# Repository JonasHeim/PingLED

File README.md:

Work in progress

# PingLED

Display the latency/delay to an internet node (e.g. Google) on a 7-segment display using a ESP8266 interfacing a TM1637.

Using the [ESP8266_NON_OS_SDK](https://github.com/espressif/ESP8266_NONOS_SDK)

## Compile application using make:
```
cd ./PingLED
make 
```
Change the variables
- COMPILE
- BOOT
- APP
- SPI_SPEED
- SPI_MODE

in ./PingLED/Makefile according to your configuration.
For additional information about the configuration see the [Expressif documentation](https://github.com/espressif/ESP8266_NONOS_SDK/tree/master/examples).

## Clean application:
```
cd ./PingLED
make clean
```

  ## Project structure:
  * ESP8266
    - Source code for the firmware on ESP8266
  * Documentation
    - Datasheets for TM1637
    - ESP8266 SDK documentation

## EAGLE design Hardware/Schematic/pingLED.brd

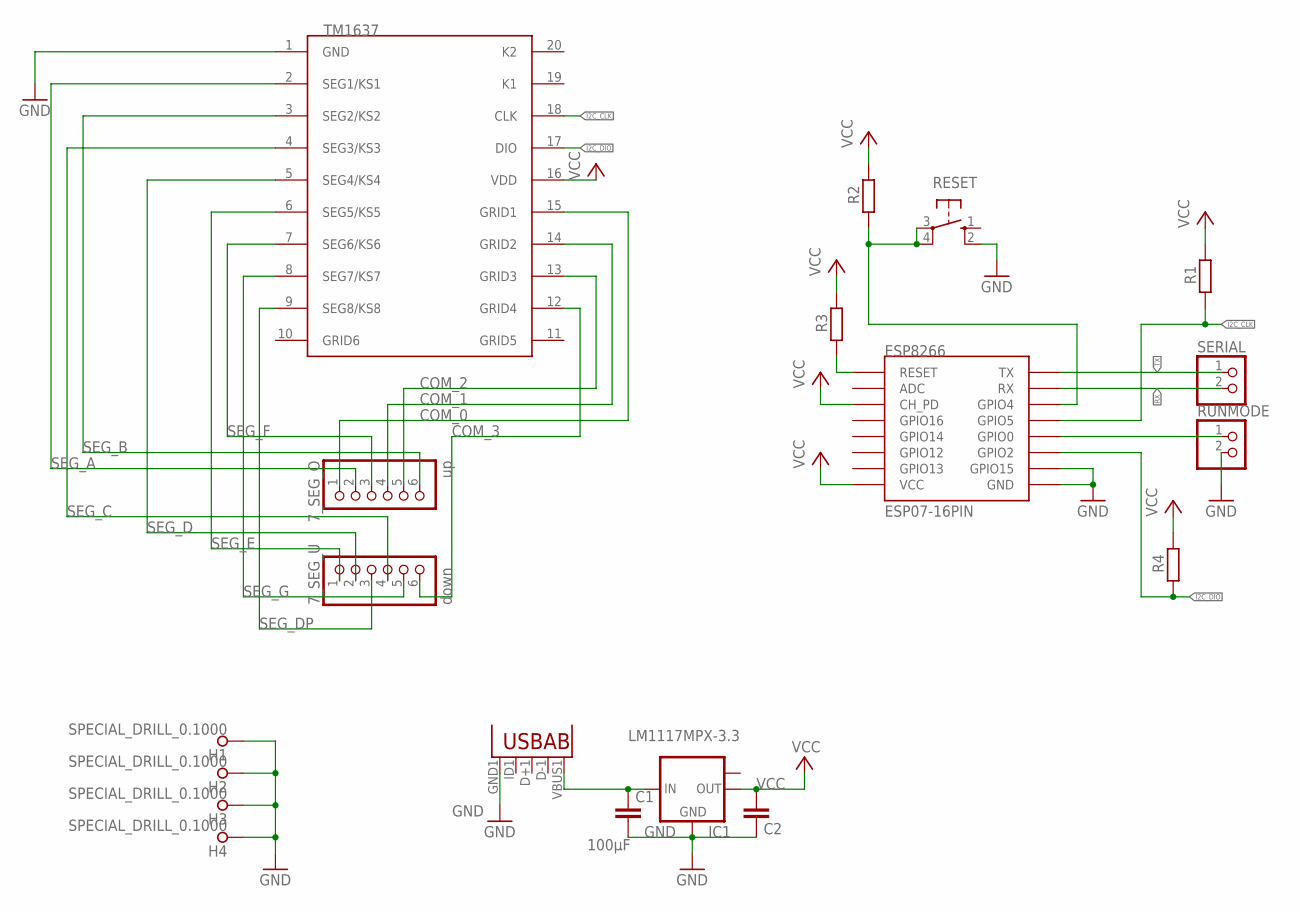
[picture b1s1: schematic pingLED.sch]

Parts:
7SEG_DRIVER: TM1637SOP20; SOIC127P1045X255-20
7_SEG_O: up; 1X06
7_SEG_U: down; 1X06
C1: 100µF; C0603
C2: C-EUC0603; C0603
ESP8266: ESP07-16PIN
H1, H2, H3, H4: SPECIAL_DRILL_0.1000; PAD_0.1000
IC1: LM1117MPX-3.3; SOT223
R1, R2, R3, R4: R-EU_R0603; R0603
RESET: 10-XX; B3F-10XX
RUNMODE: PINHD-1X2; 1X02
SERIAL: PINHD-1X2; 1X02
U1: V_IN; USB-MICRO-SMD

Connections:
COM_0: 7SEG_DRIVER.15 (GRID1), 7_SEG_O.1
COM_1: 7SEG_DRIVER.14 (GRID2), 7_SEG_O.4
COM_2: 7SEG_DRIVER.13 (GRID3), 7_SEG_O.5
COM_3: 7SEG_DRIVER.12 (GRID4), 7_SEG_U.6
GND: 7SEG_DRIVER.1 (GND), C1.2, C2.2, ESP8266.GND, ESP8266.GPIO15, H1.1, H2.1, H3.1, H4.1, IC1.1 (GND), RESET.2 (S1), RUNMODE.2, U1.GND1 (GND)
I2C_CLK: 7SEG_DRIVER.18 (CLK), ESP8266.GPIO5, R1.1
I2C_DIO: 7SEG_DRIVER.17 (DIO), ESP8266.GPIO2, R4.1
unnamed: ESP8266.GPIO0, RUNMODE.1
unnamed: ESP8266.GPIO4, R2.1, RESET.3, RESET.4 (P1)
unnamed: ESP8266.REST (RESET), R3.1
unnamed: C1.1, IC1.3 (IN), U1.VBUS1 (VBUS)
RX: ESP8266.RX, SERIAL.2
SEG_A: 7SEG_DRIVER.2 (SEG1/KS1), 7_SEG_O.2
SEG_B: 7SEG_DRIVER.3 (SEG2/KS2), 7_SEG_O.6
SEG_C: 7SEG_DRIVER.4 (SEG3/KS3), 7_SEG_U.4
SEG_D: 7SEG_DRIVER.5 (SEG4/KS4), 7_SEG_U.2
SEG_DP: 7SEG_DRIVER.9 (SEG8/KS8), 7_SEG_U.3
SEG_E: 7SEG_DRIVER.6 (SEG5/KS5), 7_SEG_U.1
SEG_F: 7SEG_DRIVER.7 (SEG6/KS6), 7_SEG_O.3
SEG_G: 7SEG_DRIVER.8 (SEG7/KS7), 7_SEG_U.5
TX: ESP8266.TX, SERIAL.1
VCC: 7SEG_DRIVER.16 (VDD), C2.1, ESP8266.CH_PD, ESP8266.VCC, IC1.2 (OUT), R1.2, R2.2, R3.2, R4.2

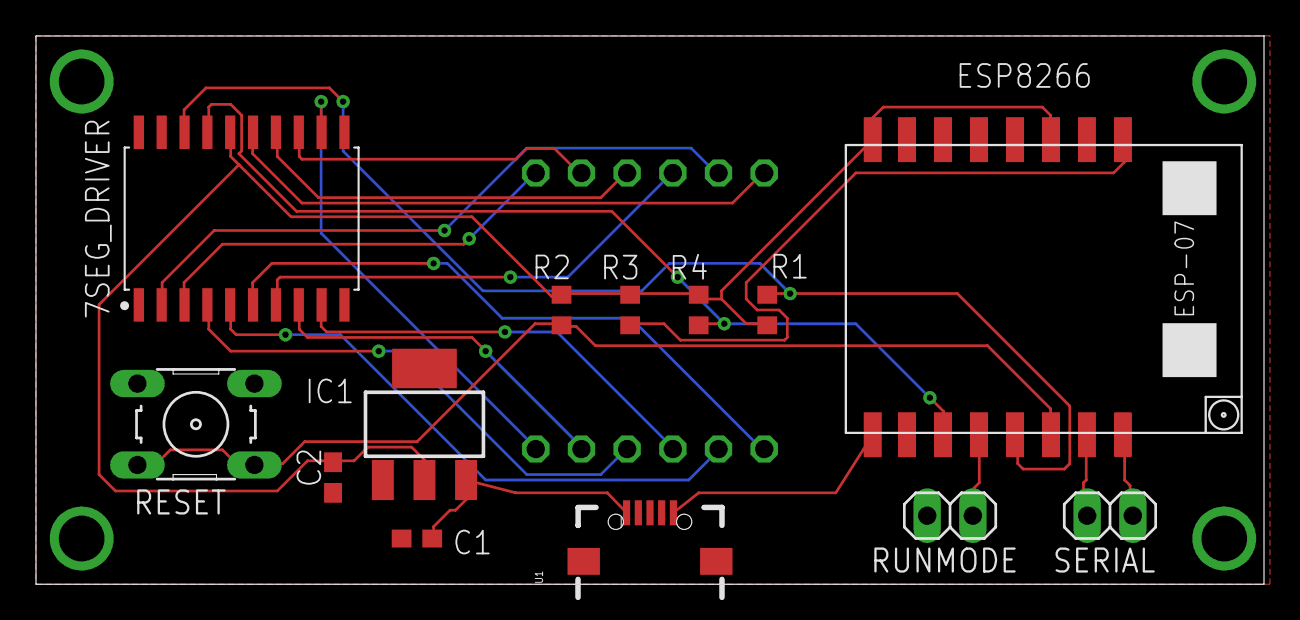
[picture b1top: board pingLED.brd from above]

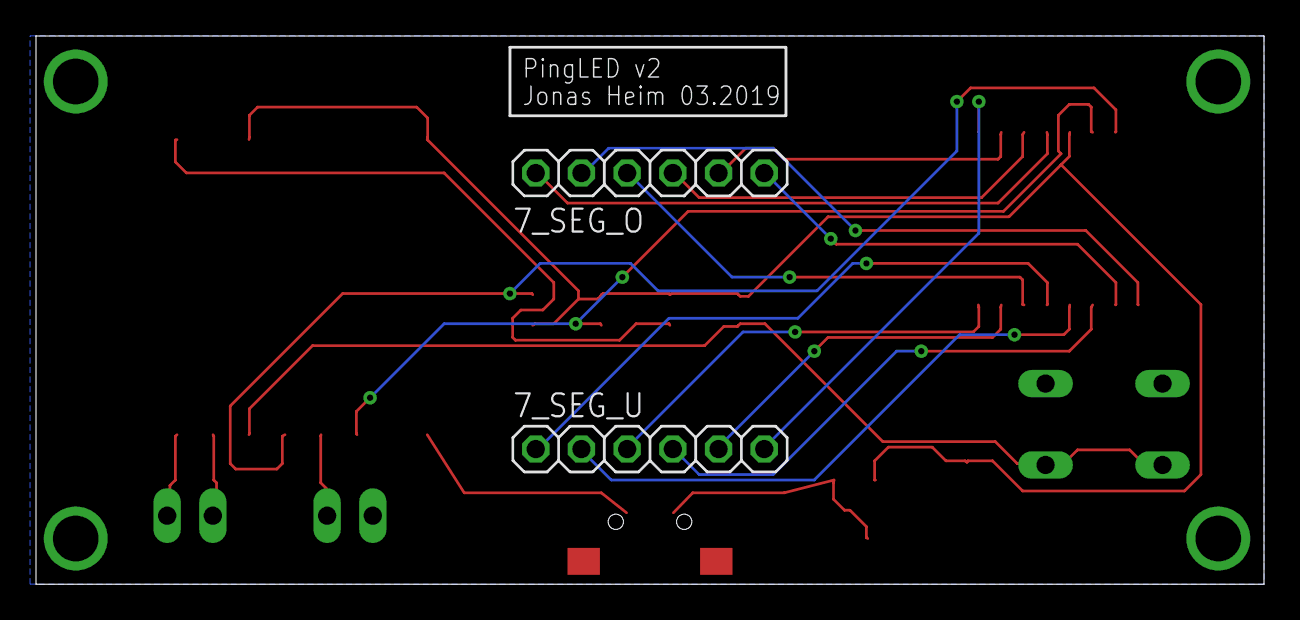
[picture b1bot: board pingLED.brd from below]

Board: 2 copper layers, 68.2 x 30.5 mm, 19 parts (2 on the bottom side), 22 nets.

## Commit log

2018-05-25 Initial commit.
2018-05-25 Fixed README.md.
2018-05-25 Fixed intendation.
2018-05-25 Fixed intendation again.
2018-05-25 Added datasheets/documentation for ESP8266 SDKs.
2018-05-25 Fixed markdown for SDK links.
2018-05-25 Added README.md for documentation directory.
2018-05-26 Added ESP8266 SDK template source code.
2018-05-26 Removed gen_misc.sh script.
2018-12-15 Added Hardware files. Added SDK. Added directory pingLED
2019-03-26 Second hardware revision done. New schematic and layout file. Cleaned up repository.
2019-03-30 Added Wi-Fi task and configuration for AccessPoint. Added Wi-Fi event callback.
2019-12-10 Added bin directory to .gitignore
2019-12-10 Moved datasheets to ./Hardware/Datasheets/. Added basic inter-task communication using simple queue. Added basic (positive) number display in TM1637 driver.
